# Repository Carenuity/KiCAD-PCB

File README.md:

Welcome to the Home Challenge (Level 2)

...

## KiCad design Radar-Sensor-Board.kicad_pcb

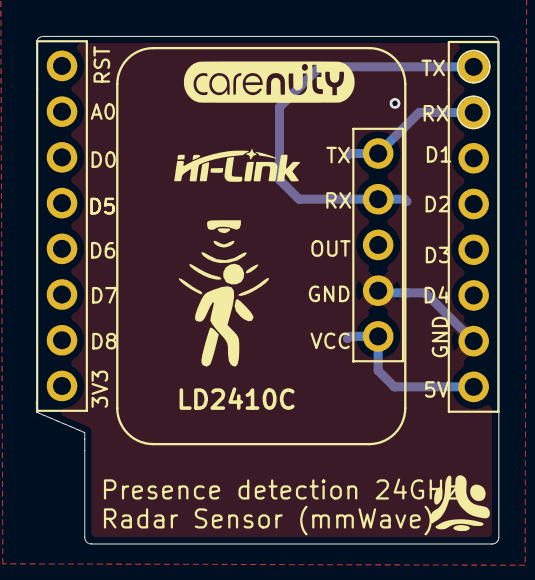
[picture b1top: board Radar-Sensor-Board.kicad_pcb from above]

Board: 2 copper layers, 25.7 x 28.2 mm, 4 parts (1 on the bottom side), 5 nets.

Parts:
J1, J2: Conn_01x08_Pin; PinHeader_1x08_P2.54mm_Vertical
J3: Conn_01x05_Pin; PinHeader_1x05_P2.54mm_Vertical_SMD_Pin1Right
J4: Conn_01x05_Pin; PinHeader_1x05_P2.54mm_Vertical

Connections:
+5V: J2.8, J3.5, J4.5
GND: J2.7, J3.4, J4.4
unnamed: J3.3, J4.3
RX: J2.1, J3.2, J4.2
TX: J2.2, J3.1, J4.1

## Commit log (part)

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2024-10-01 added image of the PCB design
2024-10-01 Video Tutorial
2024-10-02 PCB Design File for use in KiCAD
2024-10-03 Radar-Sensor-Board.kicad_pcb
2024-11-08 PCB-Design in KiCAD format
    Home-Challenge
2024-11-08 Example from THWS
    Example, how a own result could look like.
